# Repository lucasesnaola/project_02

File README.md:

# project_02
This goal of the project was to design a printed circuit board to replace the onboard circuit created in project 01. This PCB would be installed inside the RC Airboat in lieu of the current electrical components.

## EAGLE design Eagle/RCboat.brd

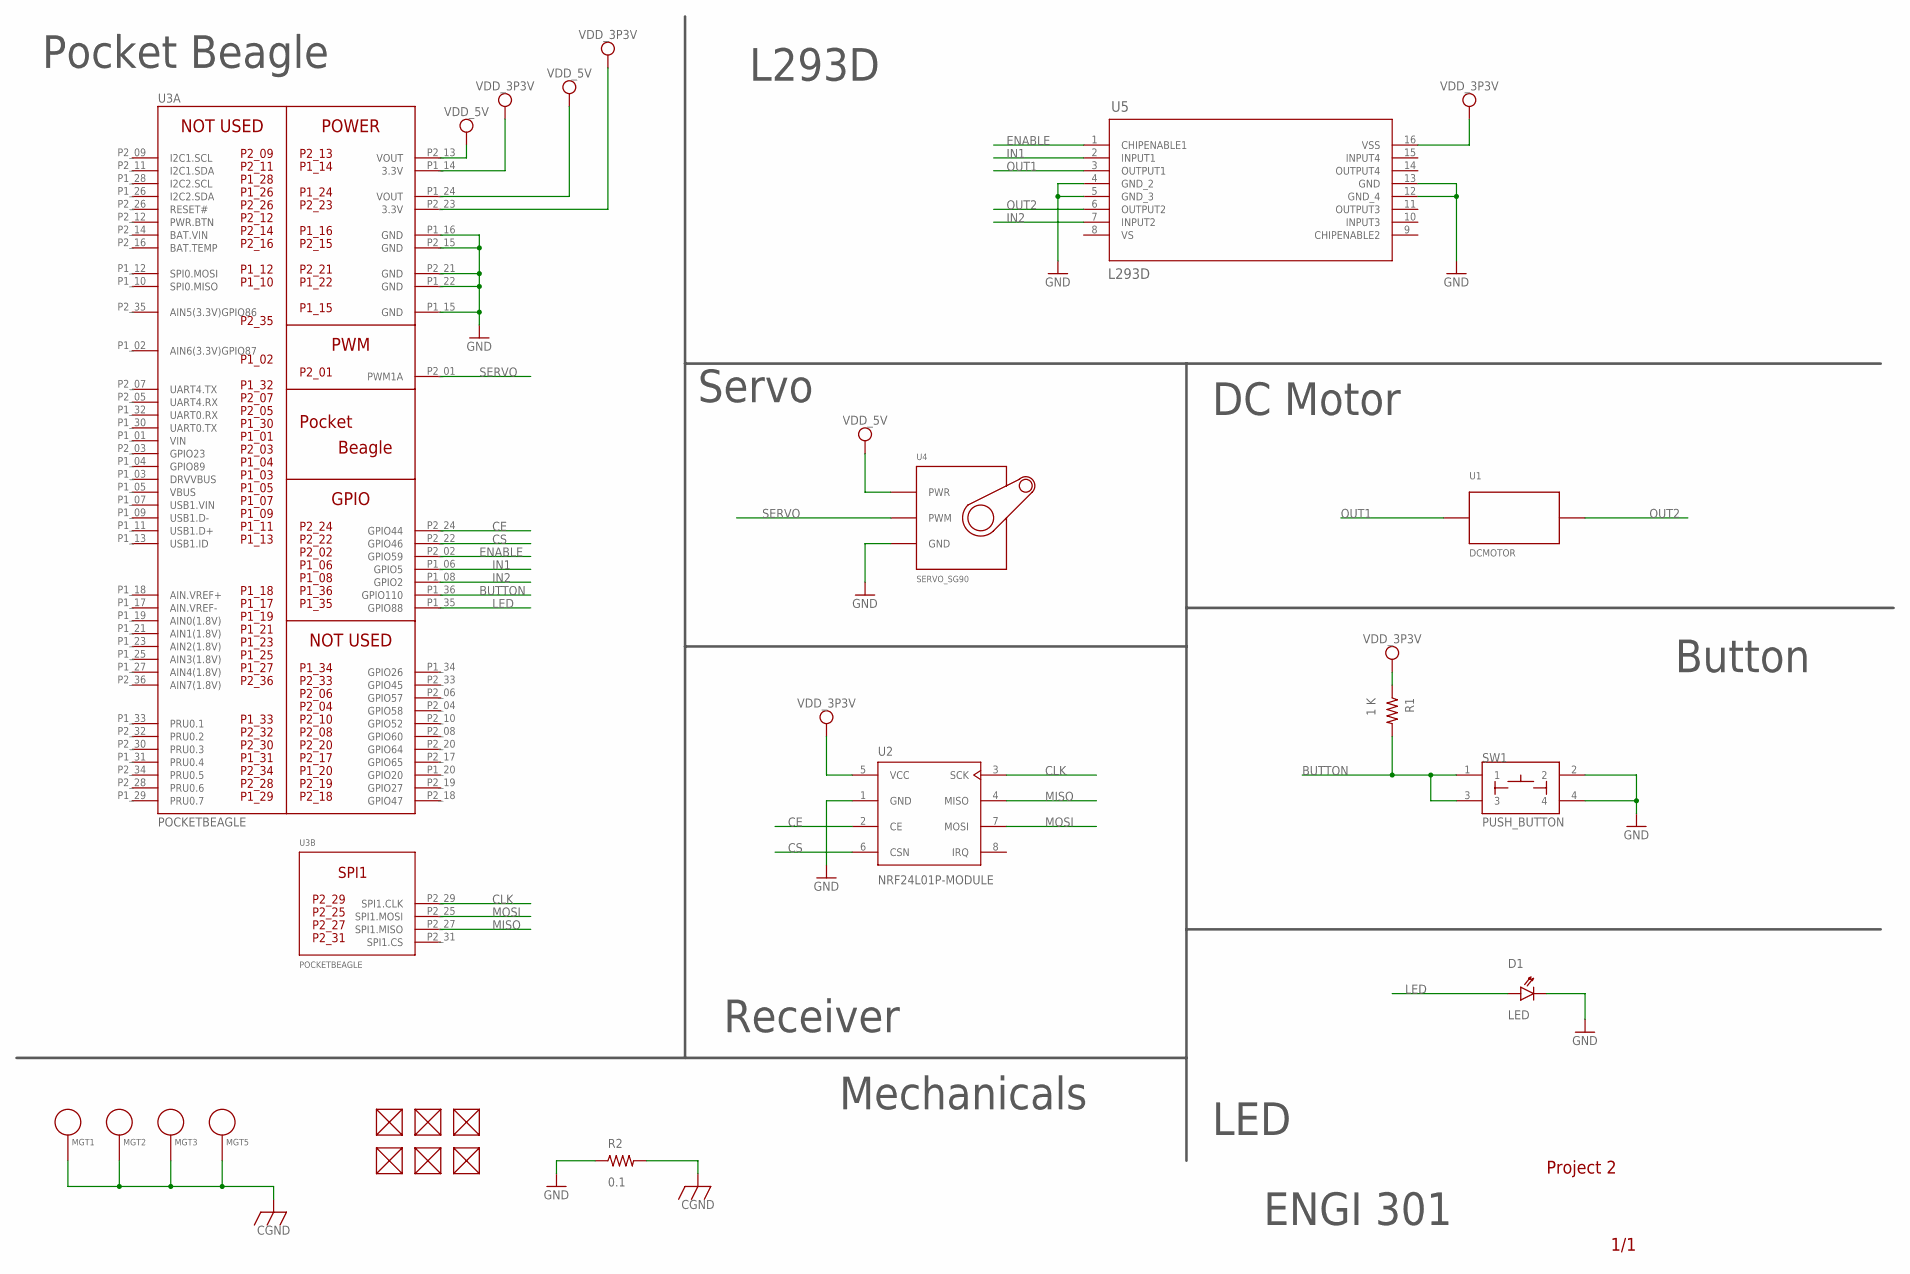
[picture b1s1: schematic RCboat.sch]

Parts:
D1: LED; EIA-STD
FUD1, FUD2, FUD3, FUD4, FUD5, FUD6: FIDUCIAL; FIDUCIAL_40MIL
MGT1, MGT2, MGT3, MGT5: MOUNTING_HOLE
R1: 1 K; R0603
R2: 0.1; R0805
SW1: PUSH_BUTTON; BUTTON_12.5MM
U1: DCMOTOR
U2: NRF24L01P-MODULE
U3: POCKETBEAGLE
U4: SERVO_SG90; SERVO-X1
U5: L293D; POWERDIP-16_STM

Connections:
BAT.VIN: U3.P2_14 (BAT.VIN)
BUTTON: R1.2, SW1.1, SW1.3, U3.P1_36 (GPIO110)
CE: U2.2 (CE), U3.P2_24 (GPIO44)
CGND: MGT1.P$1, MGT2.P$1, MGT3.P$1, MGT5.P$1, R2.2
CLK: U2.3 (SCK), U3.P2_29 (SPI1.CLK)
CS: U2.6 (CSN), U3.P2_22 (GPIO46)
ENABLE: U3.P2_02 (GPIO59), U5.1 (CHIPENABLE1)
GND: D1.CATHODE, R2.1, SW1.2, SW1.4, U2.1 (GND), U3.P1_15 (GND), U3.P1_16 (GND), U3.P1_22 (GND), U3.P2_15 (GND), U3.P2_21 (GND), U4.GND, U5.4 (GND_2), U5.5 (GND_3), U5.12 (GND_4), U5.13 (GND)
IN1: U3.P1_06 (GPIO5), U5.2 (INPUT1)
IN2: U3.P1_08 (GPIO2), U5.7 (INPUT2)
LED: D1.ANODE, U3.P1_35 (GPIO88)
MISO: U2.4 (MISO), U3.P2_27 (SPI1.MISO)
MOSI: U2.7 (MOSI), U3.P2_25 (SPI1.MOSI)
OUT1: U1.1 (V1), U5.3 (OUTPUT1)
OUT2: U1.2, U5.6 (OUTPUT2)
SERVO: U3.P2_01 (PWM1A), U4.SIG (PWM)
VDD_3P3V: R1.1, U2.5 (VCC), U3.P1_14 (3.3V), U3.P2_23 (3.3V), U5.16 (VSS)
VDD_5V: U3.P1_24 (VOUT), U3.P2_13 (VOUT), U4.PWR
VIN: U3.P1_01 (VIN)
VS: U5.8 (VS)

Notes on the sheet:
Project 2
1/1
ENGI 301
Mechanicals
Receiver
LED
Button
DC Motor
Servo
L293D
Pocket Beagle

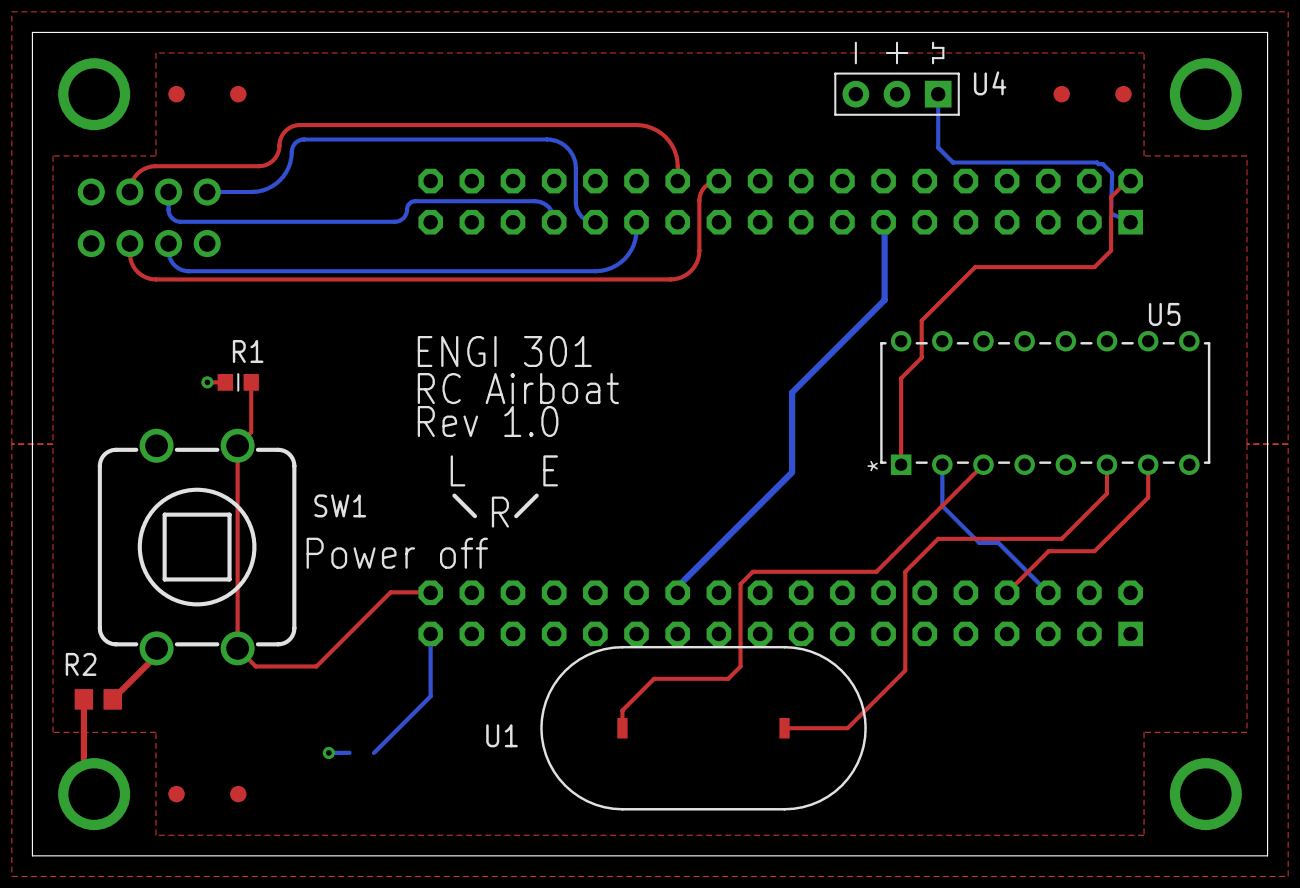
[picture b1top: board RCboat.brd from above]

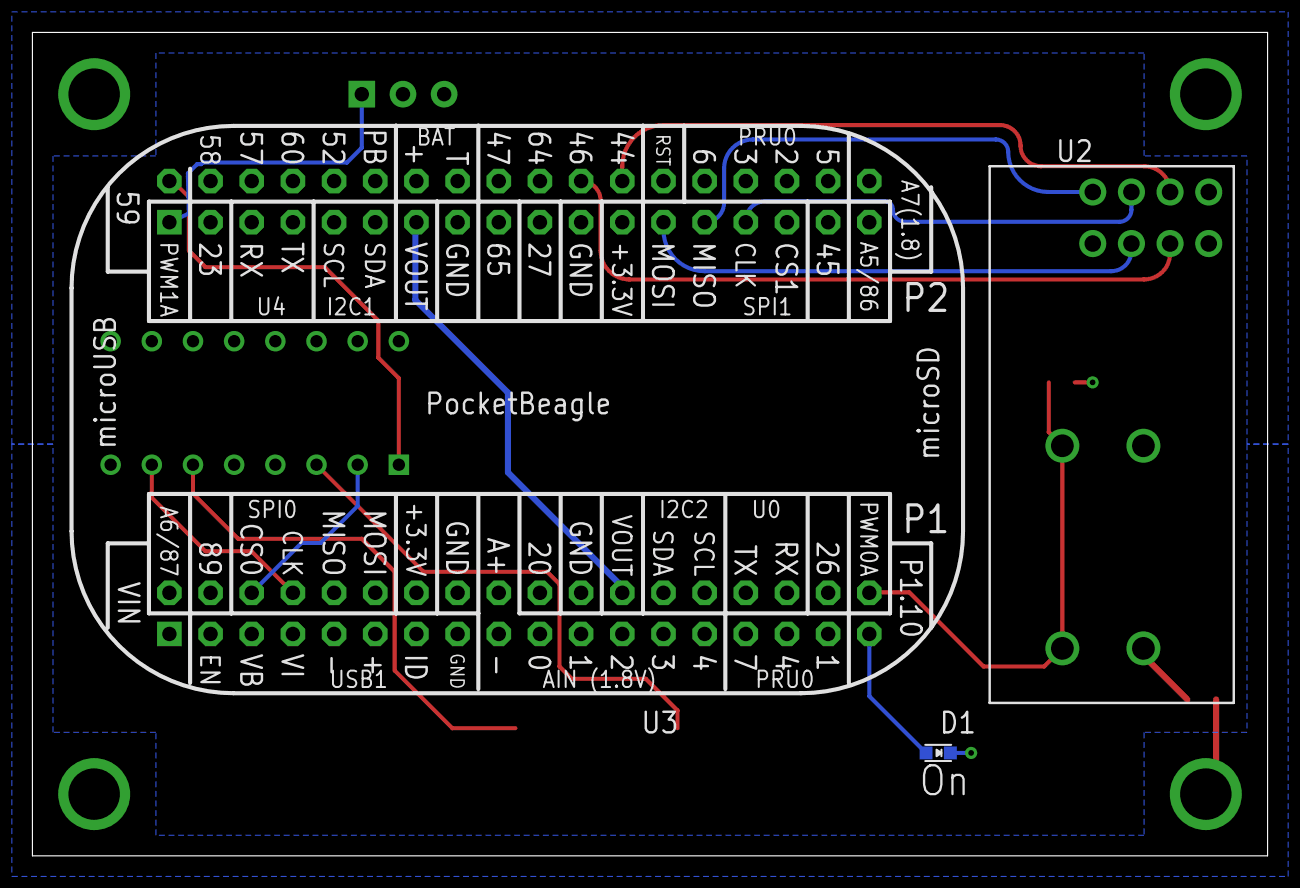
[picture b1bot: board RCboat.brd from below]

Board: 4 copper layers, 76.2 x 50.8 mm, 19 parts (3 on the bottom side), 17 nets.

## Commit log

2021-12-16 Create docs
2021-12-16 Create s

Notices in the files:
parts and their libraries:
COPYRIGHT: Copyright (C) 2021 Ultra Librarian. All rights reserved.
